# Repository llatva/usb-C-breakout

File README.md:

# usbC-breakout
USB-C breakout board

## Images

## License

This board is licensed under CERN Open Hardware License, version 2, CERN-OHL-W (weakly reciprocal). 

Please refer to LICENSE file for more information.

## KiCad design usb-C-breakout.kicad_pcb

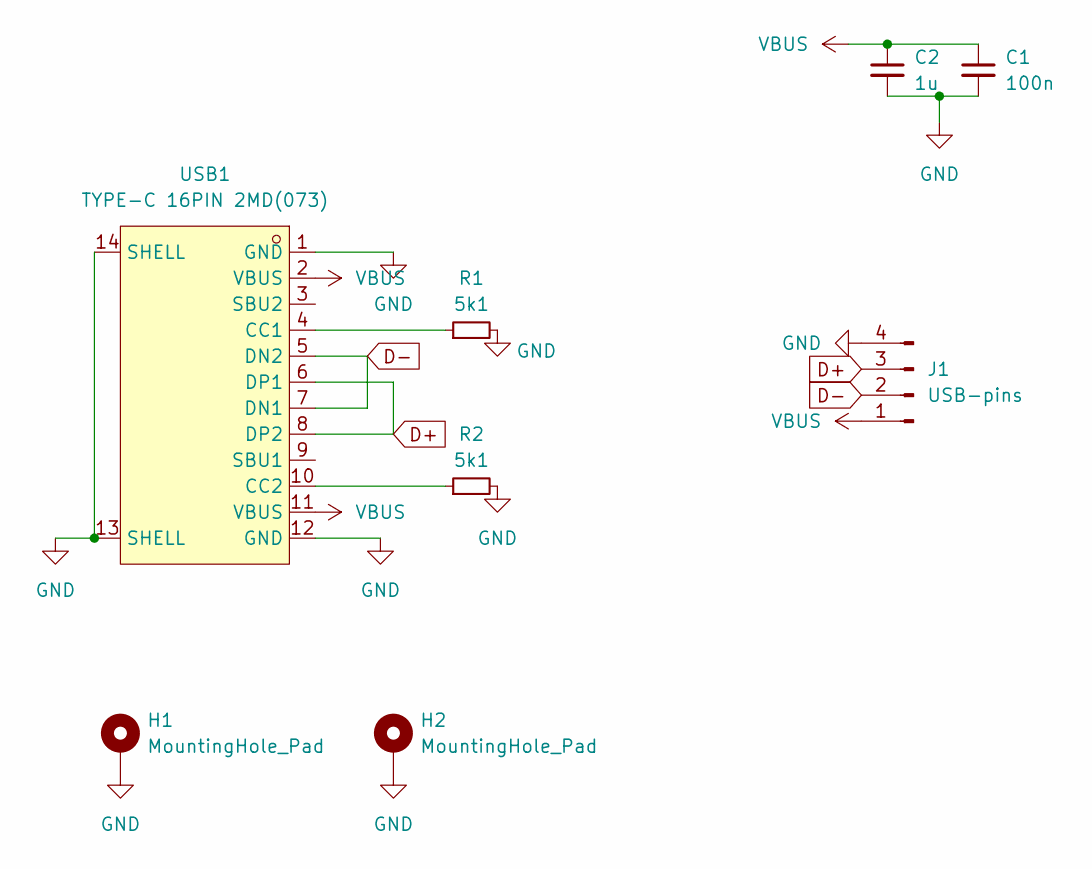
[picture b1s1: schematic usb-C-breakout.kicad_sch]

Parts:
C1: 100n; C_0805_2012Metric_Pad1.18x1.45mm_HandSolder
C2: 1u; C_0805_2012Metric_Pad1.18x1.45mm_HandSolder
H1, H2: MountingHole_Pad; MountingHole_3.2mm_M3_ISO14580_Pad_TopBottom
J1: USB-pins; PinHeader_1x04_P2.54mm_Vertical
R1, R2: 5k1; R_0805_2012Metric_Pad1.20x1.40mm_HandSolder
USB1: TYPE-C 16PIN 2MD(073); USB-C-SMD_TYPE-C-6PIN-2MD-073; LCSC Part C2765186

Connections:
D+: J1.3, USB1.6 (DP1), USB1.8 (DP2)
D-: J1.2, USB1.5 (DN2), USB1.7 (DN1)
GND: C1.2, C2.2, H1.1, H2.1, J1.4, R1.2, R2.2, USB1.1 (GND), USB1.12 (GND), USB1.13 (SHELL), USB1.14 (SHELL)
unnamed: R1.1, USB1.4 (CC1)
unnamed: R2.1, USB1.10 (CC2)
VBUS: C1.1, C2.1, J1.1, USB1.2 (VBUS), USB1.11 (VBUS)

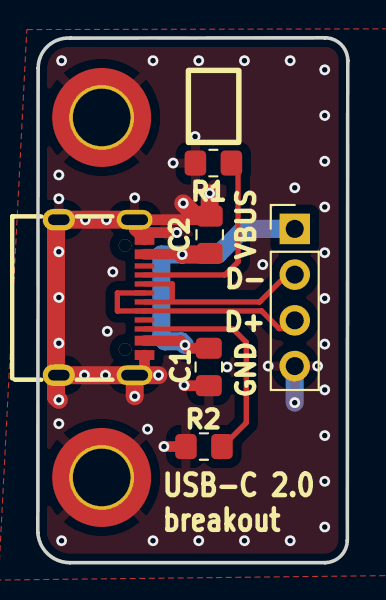
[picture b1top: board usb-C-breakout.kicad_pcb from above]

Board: 2 copper layers, 17.2 x 29.2 mm, 8 parts (0 on the bottom side), 6 nets.

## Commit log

2024-08-02 initial version to Github
2024-08-02 PCB rev to silk
2025-01-03 3d image workflow added
2025-01-03 zoom to 1
